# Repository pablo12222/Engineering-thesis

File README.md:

# Development of an electronic optimizer to control pump operation.

## Introduction

This repository contains the work and resources related to my engineering thesis titled **"Development of an electronic optimizer to control pump operation."** 

---
## Abstract 

The engineering thesis focuses on the development and construction of an electronic
(microprocessor-based) model of a setpoint controller for regulating pump performance.
The device will be implemented using a selected microcontroller with appropriately
designed input/output interfaces to interact with external devices and facilitate user
communication. The system’s operating principle can be described as follows: the
controller receives an analog 0 − 10 V signal from a regulating valve, representing the
position of the valve ball. It then compares this value with the pump’s output setpoint.
If the signal from the valve is lower than the setpoint, the device reduces the output
signal by 0.1 V at regular time intervals determined by an encoder until the target value
is reached. Conversely, if the valve ball position value exceeds the setpoint, the
controller increases the output signal by 0.1 V at the specified time intervals. The
system is equipped with three encoders for configuring operating parameters, two analog
inputs 0 − 10 V, and one analog output 0 − 10 V, ensuring precise control and
adaptation of pump performance to operational requirements. The device operates in
two modes: automatic and manual. As part of the thesis, functional tests will be
conducted using available measurement instruments and voltage generators to verify the
correct operation and compliance of the device with the design assumptions. The task is
carried out in accordance with the guidelines and for the purposes of BELIMO -
BELIMO Siłowniki S.A.

--- 

## Keywords
- transmitter,
- electronic device,
- pump control,
- microprocessor system,
- building automation.

---

## Device
This is how the developed prototype looks like:

<div style="display: flex; justify-content: center; align-items: center; gap: 10px;">

</div>

---

## Systems hardware

Ideological diagram of the operation of the transmitter:

---

The PCB was made with autodesk EAGLE software:

<div style="display: flex; justify-content: center; align-items: center; gap: 10px;">

</div>

---

The PCB enclosure was made in Autodesk Inventor:
<div style="display: flex; justify-content: center; align-items: center; gap: 10px;">

</div>

---

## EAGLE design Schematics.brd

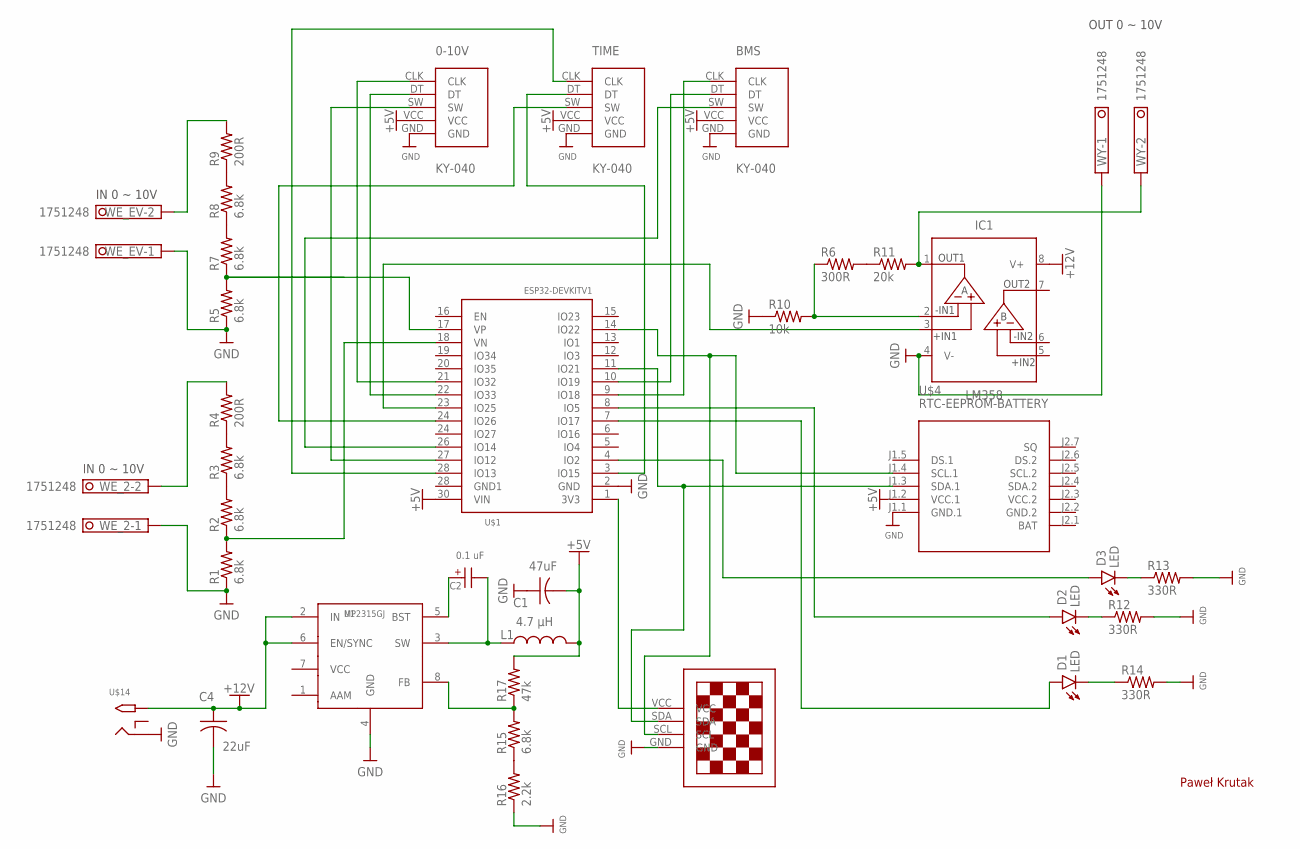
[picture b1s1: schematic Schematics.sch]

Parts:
0-10V: KY-040; KY-040-PORT
BMS: KY-040; KY-040-PORT
C1: 47uF; CAP_RADIAL_2MM
C2: 0.1 uF; WCAP-ATG5_5X11(DXL)
C4: 22uF; CAP_RADIAL_2MM
D1, D2, D3: LED; LEDRD254W60D565H860B_W90
IC1: LM358; DIP826W53P254L959H508Q8B
L1: 4.7 µH; SRN6045
R1, R2, R3, R5, R7, R8, R15: 6.8k; M0805
R4, R9: 200R; M0805
R6: 300R; M0805
R10: 10k; M0805
R11: 20k; M0805
R12, R13, R14: 330R; M0805
R16: 2.2k; M0805
R17: 47k; M0805
TIME: KY-040; KY-040-PORT
U1: MP2315GJ; SOT-23-8
U$1: ESP32DEVKITV1; ESP32-DEVKITV1
U$4: RTC-EEPROM-BATTERY; RTC_EEPROM_BATTERY
U$8: 13"OLED13"OLED; 1.3"OLED
U$14: 2.1MMJACKTHM; PJ-102A
WE_2: 1751248
WE_EV: 1751248
WY: 1751248

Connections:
+5V: 0-10V.VCC, BMS.VCC, C1.2, L1.2, R17.2, TIME.VCC, U$1.30 (VIN), U$4.J1.2 (VCC.1)
+12V: C4.1, IC1.8 (V+), U1.2 (IN), U1.6 (EN/SYNC), U$14.TIP
GND: 0-10V.GND, BMS.GND, C1.1, C4.2, IC1.4 (V-), R1.1, R5.1, R10.1, R12.2, R13.2, R14.2, R16.1, TIME.GND, U1.4 (GND), U$1.2 (GND), U$4.J1.1 (GND.1), U$8.GND, U$14.RING, WE_2.1, WE_EV.1, WY.1
GND.2: U$4.J2.2 (GND.2)
unnamed: IC1.1 (OUT1), R11.2, WY.2
unnamed: R6.2, R11.1
unnamed: IC1.2 (-IN1), R6.1, R10.2
unnamed: IC1.3 (+IN1), U$1.23 (IO25)
unnamed: R2.2, R3.1
unnamed: R5.2, R7.1, U$1.17 (VP)
unnamed: R4.2, WE_2.2
unnamed: R3.2, R4.1
unnamed: R7.2, R8.1
unnamed: R1.2, R2.1, U$1.18 (VN)
unnamed: R8.2, R9.1
unnamed: U$1.1 (3V3), U$8.VCC
unnamed: U$1.14 (IO22), U$4.J1.4 (SCL.1), U$8.SCL
unnamed: U$1.11 (IO21), U$4.J1.3 (SDA.1), U$8.SDA
unnamed: 0-10V.CLK, U$1.21 (IO32)
unnamed: BMS.CLK, U$1.9 (IO18)
unnamed: BMS.DT, U$1.10 (IO19)
unnamed: 0-10V.DT, U$1.22 (IO33)
unnamed: BMS.SW, U$1.26 (IO14)
unnamed: 0-10V.SW, U$1.27 (IO12)
unnamed: D2.1 (A), U$1.8 (IO5)
unnamed: R15.1, R16.2
unnamed: D1.1 (A), U$1.7 (IO17)
unnamed: R9.2, WE_EV.2
unnamed: D3.2 (C), R13.1
unnamed: D2.2 (C), R12.1
unnamed: D3.1 (A), U$1.4 (IO2)
unnamed: D1.2 (C), R14.1
unnamed: TIME.CLK, U$1.28 (IO13)
unnamed: TIME.DT, U$1.3 (IO15)
unnamed: TIME.SW, U$1.24 (IO27)
unnamed: C2.1 (+), U1.5 (BST)
unnamed: R15.2, R17.1, U1.8 (FB)
unnamed: C2.2 (-), L1.1, U1.3 (SW)
VCC.2: U$4.J2.3 (VCC.2)

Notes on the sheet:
OUT 0 ~ 10V
Paweł Krutak
IN 0 ~ 10V

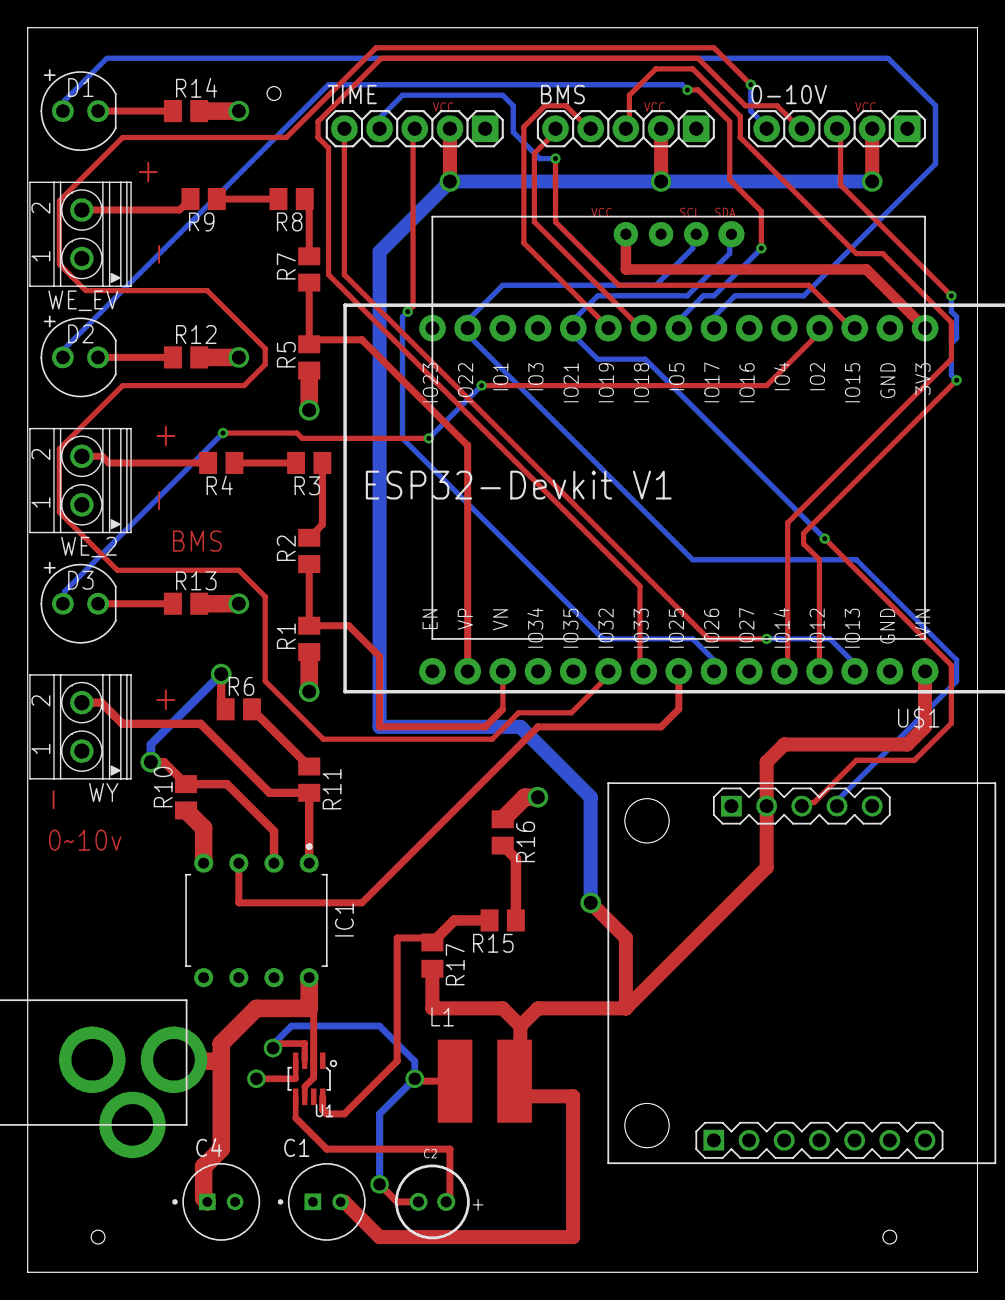
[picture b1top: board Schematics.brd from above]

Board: 2 copper layers, 68.6 x 89.8 mm, 36 parts (0 on the bottom side), 37 nets.

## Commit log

2025-05-26 Hardware
2025-05-26 Create Hardware

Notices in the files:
parts and their libraries:
Wurth_Capacitors_WCAP-ATG5: Copyright: Würth Elektronik
diy-modules: Released under the Creative Commons Attribution 4.0 International License: http://creativecommons.org/licenses/by/4.0
